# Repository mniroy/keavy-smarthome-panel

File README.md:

# KEAVY Smart Home Modular DIN-Rail & Standalone PLC Automation Platform

DRC-verified (0 violations, 0 unconnected items) industrial-grade DIN-Rail ESPHome & Home Assistant hardware ecosystem:

## 1. [`standalone/`](standalone/) — All-in-One 16-Channel LAN Relay Driver
- **Single-board `152.0 × 72.0 mm` (UM72 DIN-Rail)** exact replica of the 6-CH dimmer form factor.
- Built-in ESP32 DevKit + W5500 Ethernet LAN + `MCP23017` + `2× ULN2803G` + 16 status LEDs + 3.81mm screw terminals for **Omron G2R-1-E 24VDC NPN** relay modules.
- See [`standalone/README.md`](standalone/README.md).

## 2. [`modular/`](modular/) — Side-by-Side Chainable PLC Ecosystem (`KEAVY-BUS`, `DC3-10P`)
- Sized specifically to fit off-the-shelf DIN-Rail PLC enclosures (**SZOMK AK-P-08 `145×90×40mm`** & **AK-P-01 `115×90×40mm`**) as well as **UM72** carriers.
- Interconnected side-by-side via keyed, anti-reverse **Shrouded IDC Box Headers (`DC3-10P`, 2×5 2.54mm)** + standard `FC-10P` flat ribbon jumpers:
  - [`modular/brain/`](modular/brain/) — **KEAVY-BRAIN** (`120 × 72 mm`): ESP32 + W5500 LAN + 24V→5V Buck + `KEAVY-BUS` Master + Hot-Swap LDO & PTC
  - [`modular/relay_16ch/`](modular/relay_16ch/) — **KEAVY-RELAY16** (`96 × 72 mm`): 2500V Galvanic Isolated 16-CH NPN Relay Driver (`MCP23017` + `2× ULN2803G`, DIP `0x20–0x27`)
  - [`modular/dimmer_6ch/`](modular/dimmer_6ch/) — **KEAVY-DIMMER6** (`96 × 72 mm`): 2500V Galvanic Isolated 6-CH 60W/CH LED Dimmer (`PCA9685PW` + `6× AOD4184A`, DIP `0x40–0x47`)
  - [`modular/input_12a4/`](modular/input_12a4/) — **KEAVY-INPUT12A4** (`120 × 72 mm`): 12-CH Isolated Digital Inputs (Opto-Isolated 24V Dry/Wet) + 4-CH Industrial Analog Inputs (`ADS1115` 16-bit ADC, 0–10V / 4–20mA selectable)
- See [`modular/README.md`](modular/README.md).

## 3. [`PCB Design Rule/`](PCB%20Design%20Rule/) — Comprehensive PCB & EMI/EMC Design Guidelines
- Complete reference library covering:
  - `01-EMI-EMC-Certification-Rules.md`: Return paths, split-plane rules, certification checklists.
  - `02-Grounding-Return-Current-Stackup.md`: Star grounding, stitching vias, 2-layer and 4-layer stackups.
  - `03-Power-Integrity-Buck-Decoupling-Thermal.md`: SW node loop minimization, thermal vias, decoupling.
  - `04-High-Speed-Crystal-RF-Ethernet.md`: MII/RMII/SPI, differential impedance, isolation moat.
  - `05-Galvanic-Isolation-Creepage-Clearance-ESD.md`: IEC 60664-1 clearance/creepage, TVS diode layout.
  - `06-Routing-Geometry-DFM-DFA-JLCPCB.md`: Trace chamfering, acid traps, teardrops, SMD clearances.
  - `07-KEAVY-Project-Case-Study-and-Checklist.md`: Implementation record and DRC verification summary.
- See [`PCB Design Rule/README.md`](PCB%20Design%20Rule/README.md).

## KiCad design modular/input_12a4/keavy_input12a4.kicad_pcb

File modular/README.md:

# KEAVY Modular DIN-Rail PLC Ecosystem (REV 2.0 — Industrial Galvanic Isolation & Hot-Swap Bus)

A modular, side-by-side chainable **DIN-Rail Smart Automation Ecosystem** built for **ESPHome** and **Home Assistant**, sized to fit off-the-shelf **PLC DIN-Rail Enclosures** (`SZOMK AK-P-08` & `AK-P-01`) as well as open **UM72 (72mm)** DIN-Rail carriers.

---

## REV 2.0 Industrial Upgrades

1. **Full 2500 Vrms Galvanic Isolation (`ADuM1250ARZ` + `B0505S-1W`) on Every Slave Module**:
   - **Zero Ground Loop**: Bus ground (`GND_BUS`) and 24V high-current power ground (`GND_ISO`) are **100% electrically separated** on both `KEAVY-RELAY16` and `KEAVY-DIMMER6`.
   - **Isolated Power**: Each slave uses a `B0505S-1W` (5V→5V 1W isolated DC-DC) + local `AMS1117-3.3` (`+3V3_ISO`) to power its `MCP23017` / `PCA9685PW` and `ADuM1250ARZ` Side 2.
   - **Isolated Bidirectional I²C**: `ADuM1250ARZ` (pin-compatible with `ISO1540DR` / `CA-IS3020S`) isolates `SDA` & `SCL` up to 2500 Vrms with dedicated `4.7kΩ` pull-ups on the isolated side.
2. **Hot-Swap & Short-Circuit Protection on `KEAVY-BRAIN`**:
   - **Dedicated Bus LDO (`U5_BUS`, `AMS1117-3.3`)**: `+3V3_BUS` is generated independently from the ESP32 DevKit's internal 3.3V regulator — hot-plugging or shorting a slave module will **not** brownout or reset the ESP32.
   - **Dual 500mA SMD PTC Polyfuses (`F_5V`, `F_3V3`)**: Auto-resetting overcurrent protection on both `+5V_BUS` and `+3V3_BUS`.
3. **EMI & ESD Hardening for Relay/Contactor Panels**:
   - **EMI-Shielded `DC3-10P` Pinout**: `GND_BUS` (Pin 8) physically separates `I2C_SDA` (Pin 7) from `I2C_SCL` (Pin 9) inside the 10-pin IDC ribbon cable.
   - **Strong `2.2kΩ` Pull-Ups + `47Ω` Series Damping Resistors** (`R_DSDA`, `R_DSCL`) + **`USBLC6-2SC6` ESD TVS Diode** (`D_ESD`) right at the `J_BUS_OUT` connector.
   - **100 kHz I²C Bus Clock** configured in [`firmware/keavy_modular.yaml`](firmware/keavy_modular.yaml) for maximum noise margin.

---

## System Architecture (`KEAVY-BUS` REV 2.0)

```
┌───────────────────────────┐   DC3-10P IDC    ┌────────────────────────┐   DC3-10P IDC    ┌────────────────────────┐
│     KEAVY-BRAIN V2.0      │ ═══════════════▶ │   KEAVY-RELAY16 V2.0   │ ═══════════════▶ │   KEAVY-DIMMER6 V2.0   │
│  120.0 × 72.0 mm          │  (Hot-Swap Bus)  │   96.0 × 72.0 mm       │  (Hot-Swap Bus)  │   96.0 × 72.0 mm       │
│  ESP32 + W5500 + U5_BUS   │                  │  2500V ISO (ADuM1250 + │                  │  2500V ISO (ADuM1250 + │
│  2×500mA PTC + USBLC6 ESD │                  │  B0505S) + MCP23017 +  │                  │  B0505S) + PCA9685 +   │
│  Fits: AK-P-08 / UM72     │                  │  2×ULN2803G (16-CH)    │                  │  6×AOD4184A (60W/CH)   │
└───────────────────────────┘                  └────────────────────────┘                  └────────────────────────┘
```

### Modules Included (All 0 DRC Violations, 0 Unconnected Items)

| Module | PCB Size | Market PLC Casing Fit | Function | Addressing / Scalability |
|---|---|---|---|---|
| **KEAVY-BRAIN** | `120.0 × 72.0 mm` | **SZOMK AK-P-08** (`145×90×40mm`) & **UM72** | ESP32 DevKit + W5500 LAN + RJ45 + 24V→5V Buck (`XL1509-5.0`) + Dedicated `U5_BUS` 3.3V + Dual `500mA PTC` + `USBLC6-2SC6` ESD | 1 Brain per bus (1 Ethernet cable) |
| **KEAVY-RELAY16** | `96.0 × 72.0 mm` | **SZOMK AK-P-01** (`115×90×40mm`) & **UM72** | **2500Vrms Isolated** 16-CH 24VDC NPN Relay Driver (`B0505S-1W` + `ADuM1250ARZ` + `MCP23017` + `2× ULN2803G`) for Omron G2R-1-E | 3-bit DIP `SW1`: `0x20`–`0x27` (up to **8 boards = 128 relays**) |
| **KEAVY-DIMMER6** | `96.0 × 72.0 mm` | **SZOMK AK-P-01** (`115×90×40mm`) & **UM72** | **2500Vrms Isolated** 6-CH 60W/CH LED Dimmer (`B0505S-1W` + `ADuM1250ARZ` + `PCA9685PW` 1.526kHz + `6× AOD4184A`, 15A fuse) | 3-bit DIP `SW1`: `0x40`–`0x47` (up to **8 boards = 48 dimmers**) |
| **KEAVY-INPUT12A4** | `120.0 × 72.0 mm` | **SZOMK AK-P-08** (`145×90×40mm`) & **UM72** | **2500Vrms Isolated** 12-CH DI (3× `TLP281-4` optocouplers) + 4-CH Industrial AI (`ADS1115` 16-bit ADC, 0–10V / 4–20mA selectable) + `ADuM1250ARZ` + `B0505S-1W` | `MCP23017` DIP `0x20`–`0x27`, `ADS1115` ADDR Pin `0x48`–`0x4B` |

### Standardized 10-Pin `KEAVY-BUS` REV 2.0 (`DC3-10P` Shrouded Keyed IDC Header)

| Pin | Signal | Pin | Signal |
|---|---|---|---|
| **1** | `+5V_BUS` (500mA PTC) | **2** | `+5V_BUS` (500mA PTC) |
| **3** | `GND_BUS` | **4** | `GND_BUS` |
| **5** | `+3V3_BUS` (Dedicated LDO + 500mA PTC) | **6** | `GND_BUS` (Shield) |
| **7** | `I2C_SDA` (`GPIO21`, 47Ω + ESD) | **8** | `GND_BUS` **(EMI Shield between SDA & SCL)** |
| **9** | `I2C_SCL` (`GPIO22`, 47Ω + ESD) | **10** | `BUS_INT` (`GPIO16`) |

*(High-current 24V coil/LED power is fed separately to each slave module's own `J1` 24V terminal block, with `GND_ISO` 100% galvanically isolated from `GND_BUS`.)*

---

## Firmware & Manufacturing Files

- **Unified ESPHome Config (100 kHz I²C)**: [`firmware/keavy_modular.yaml`](firmware/keavy_modular.yaml)
- **JLCPCB Packages** (Gerber ZIP + BOM with LCSC Part # + CPL):
  - `brain/manufacturing/jlcpcb/`
  - `relay_16ch/manufacturing/jlcpcb/`
  - `dimmer_6ch/manufacturing/jlcpcb/`

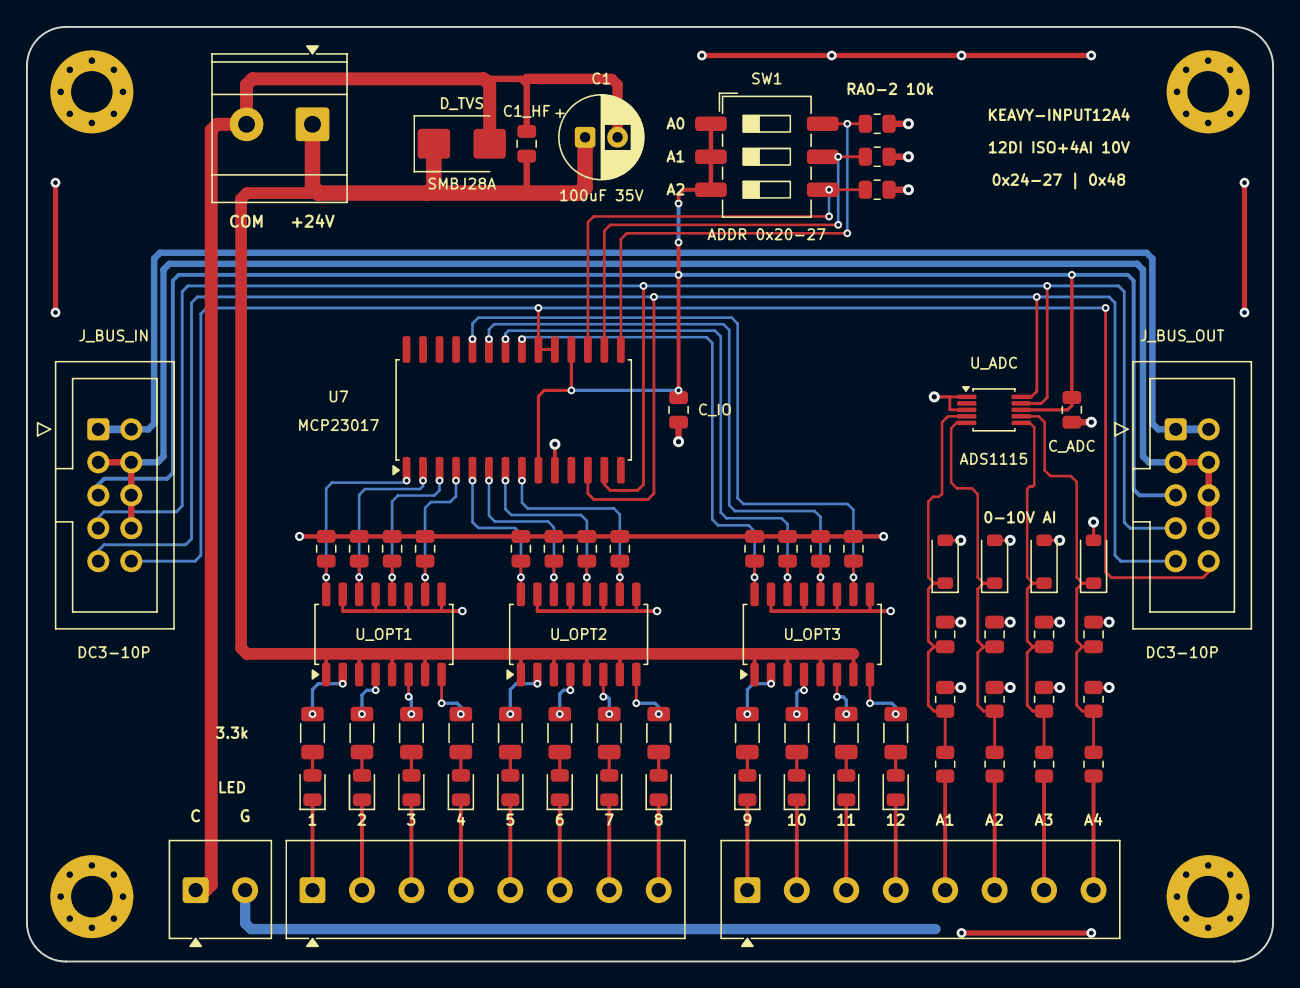
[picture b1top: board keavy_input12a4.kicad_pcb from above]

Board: 2 copper layers, 96.0 x 72.0 mm, 76 parts (0 on the bottom side), 67 nets.

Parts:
C1: 100uF 35V; CP_Radial_D6.3mm_P2.50mm
C1_HF: 100nF 50V; C_0805_2012Metric
CA1, CA2, CA3, CA4: 100nF; C_0805_2012Metric
CD1, CD2, CD3, CD4, CD5, CD6, CD7, CD8, CD9, CD10, CD11, CD12: 100nF; C_0805_2012Metric
C_ADC: 100nF; C_0805_2012Metric
C_IO: 100nF; C_0805_2012Metric
DA1, DA2, DA3, DA4: BZT52C3V3; D_SOD-123
D_TVS: SMBJ28A; D_SMB
H1, H2, H3, H4: M3; MountingHole_3.2mm_M3_Pad_Via
J1: 24V_IN; TerminalBlock_Phoenix_MKDS-3-2-5.08_1x02_P5.08mm_Horizontal
J2: COM_GND; TerminalBlock_Phoenix_MKDS-1-2-3.81_1x02_P3.81mm_Horizontal
J3: DI1-DI8; TerminalBlock_Phoenix_MKDS-1-8-3.81_1x08_P3.81mm_Horizontal
J4: DI9-12_AI1-4; TerminalBlock_Phoenix_MKDS-1-8-3.81_1x08_P3.81mm_Horizontal
J_BUS_IN: DC3-10P; IDC-Header_2x05_P2.54mm_Vertical
J_BUS_OUT: DC3-10P; IDC-Header_2x05_P2.54mm_Vertical
LED1, LED2, LED3, LED4, LED5, LED6, LED7, LED8, LED9, LED10, LED11, LED12: LED; LED_0805_2012Metric
RA0, RA1, RA2: 10k; R_0805_2012Metric
RAH1, RAH2, RAH3, RAH4: 22k 1%; R_0805_2012Metric
RAL1, RAL2, RAL3, RAL4: 10k 1%; R_0805_2012Metric
RD1, RD2, RD3, RD4, RD5, RD6, RD7, RD8, RD9, RD10, RD11, RD12: 3.3k; R_1206_3216Metric
SW1: ADDR 0x20-27; SW_DIP_SPSTx03_Slide_6.7x9.18mm_W8.61mm_P2.54mm_LowProfile
U7: MCP23017; SOIC-28W_7.5x17.9mm_P1.27mm
U_ADC: ADS1115; MSOP-10_3x3mm_P0.5mm
U_OPT1, U_OPT2, U_OPT3: TLP281-4; SOP-16_4.4x10.4mm_P1.27mm

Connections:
+3V3_BUS: C_ADC.1, C_IO.1, J_BUS_IN.5, J_BUS_OUT.5, SW1.1, SW1.2, SW1.3, U7.9, U7.18, U_ADC.8
+5V_BUS: J_BUS_IN.1, J_BUS_IN.2, J_BUS_OUT.1, J_BUS_OUT.2
+24V_FIELD: C1.1, C1_HF.1, D_TVS.1, J1.1, U_OPT1.1, U_OPT1.3, U_OPT1.5, U_OPT1.7, U_OPT2.1, U_OPT2.3, U_OPT2.5, U_OPT2.7, U_OPT3.1, U_OPT3.3, U_OPT3.5, U_OPT3.7
ADC_AIN0: CA1.1, DA1.1, RAH1.2, RAL1.1, U_ADC.4
ADC_AIN1: CA2.1, DA2.1, RAH2.2, RAL2.1, U_ADC.5
ADC_AIN2: CA3.1, DA3.1, RAH3.2, RAL3.1, U_ADC.6
ADC_AIN3: CA4.1, DA4.1, RAH4.2, RAL4.1, U_ADC.7
ADDR_A0: RA0.1, SW1.6, U7.15
ADDR_A1: RA1.1, SW1.5, U7.16
ADDR_A2: RA2.1, SW1.4, U7.17
AI1_0_10V: J4.5, RAH1.1
AI2_0_10V: J4.6, RAH2.1
AI3_0_10V: J4.7, RAH3.1
AI4_0_10V: J4.8, RAH4.1
BUS_INT: J_BUS_IN.10, J_BUS_OUT.10, U7.19, U7.20
DI1_FIELD: J3.1, LED1.1
DI1_LED: LED1.2, RD1.2
DI1_MCU: CD1.1, U7.1, U_OPT1.16
DI1_OPTO_A: RD1.1, U_OPT1.2
DI2_FIELD: J3.2, LED2.1
DI2_LED: LED2.2, RD2.2
DI2_MCU: CD2.1, U7.2, U_OPT1.14
DI2_OPTO_A: RD2.1, U_OPT1.4
DI3_FIELD: J3.3, LED3.1
DI3_LED: LED3.2, RD3.2
DI3_MCU: CD3.1, U7.3, U_OPT1.12
DI3_OPTO_A: RD3.1, U_OPT1.6
DI4_FIELD: J3.4, LED4.1
DI4_LED: LED4.2, RD4.2
DI4_MCU: CD4.1, U7.4, U_OPT1.10
DI4_OPTO_A: RD4.1, U_OPT1.8
DI5_FIELD: J3.5, LED5.1
DI5_LED: LED5.2, RD5.2
DI5_MCU: CD5.1, U7.5, U_OPT2.16
DI5_OPTO_A: RD5.1, U_OPT2.2
DI6_FIELD: J3.6, LED6.1
DI6_LED: LED6.2, RD6.2
DI6_MCU: CD6.1, U7.6, U_OPT2.14
DI6_OPTO_A: RD6.1, U_OPT2.4
DI7_FIELD: J3.7, LED7.1
DI7_LED: LED7.2, RD7.2
DI7_MCU: CD7.1, U7.7, U_OPT2.12
DI7_OPTO_A: RD7.1, U_OPT2.6
DI8_FIELD: J3.8, LED8.1
DI8_LED: LED8.2, RD8.2
DI8_MCU: CD8.1, U7.8, U_OPT2.10
DI8_OPTO_A: RD8.1, U_OPT2.8
DI9_FIELD: J4.1, LED9.1
DI9_LED: LED9.2, RD9.2
DI9_MCU: CD9.1, U7.21, U_OPT3.16
DI9_OPTO_A: RD9.1, U_OPT3.2
DI10_FIELD: J4.2, LED10.1
DI10_LED: LED10.2, RD10.2
DI10_MCU: CD10.1, U7.22, U_OPT3.14
DI10_OPTO_A: RD10.1, U_OPT3.4
DI11_FIELD: J4.3, LED11.1
DI11_LED: LED11.2, RD11.2
DI11_MCU: CD11.1, U7.23, U_OPT3.12
DI11_OPTO_A: RD11.1, U_OPT3.6
DI12_FIELD: J4.4, LED12.1
DI12_LED: LED12.2, RD12.2
DI12_MCU: CD12.1, U7.24, U_OPT3.10
DI12_OPTO_A: RD12.1, U_OPT3.8
GND_BUS: CA1.2, CA2.2, CA3.2, CA4.2, CD1.2, CD2.2, CD3.2, CD4.2, CD5.2, CD6.2, CD7.2, CD8.2, CD9.2, CD10.2, CD11.2, CD12.2, C_ADC.2, C_IO.2, DA1.2, DA2.2, DA3.2, DA4.2, H1.1, H2.1, H3.1, H4.1, J2.2, J_BUS_IN.3, J_BUS_IN.4, J_BUS_IN.6, J_BUS_IN.8, J_BUS_OUT.3, J_BUS_OUT.4, J_BUS_OUT.6, J_BUS_OUT.8, RA0.2, RA1.2, RA2.2, RAL1.2, RAL2.2, RAL3.2, RAL4.2, U7.10, U_ADC.1, U_ADC.3, U_OPT1.9, U_OPT1.11, U_OPT1.13, U_OPT1.15, U_OPT2.9, U_OPT2.11, U_OPT2.13, U_OPT2.15, U_OPT3.9, U_OPT3.11, U_OPT3.13, U_OPT3.15
GND_FIELD: C1.2, C1_HF.2, D_TVS.2, J1.2, J2.1
I2C_SCL: J_BUS_IN.9, J_BUS_OUT.9, U7.12, U_ADC.10
I2C_SDA: J_BUS_IN.7, J_BUS_OUT.7, U7.13, U_ADC.9

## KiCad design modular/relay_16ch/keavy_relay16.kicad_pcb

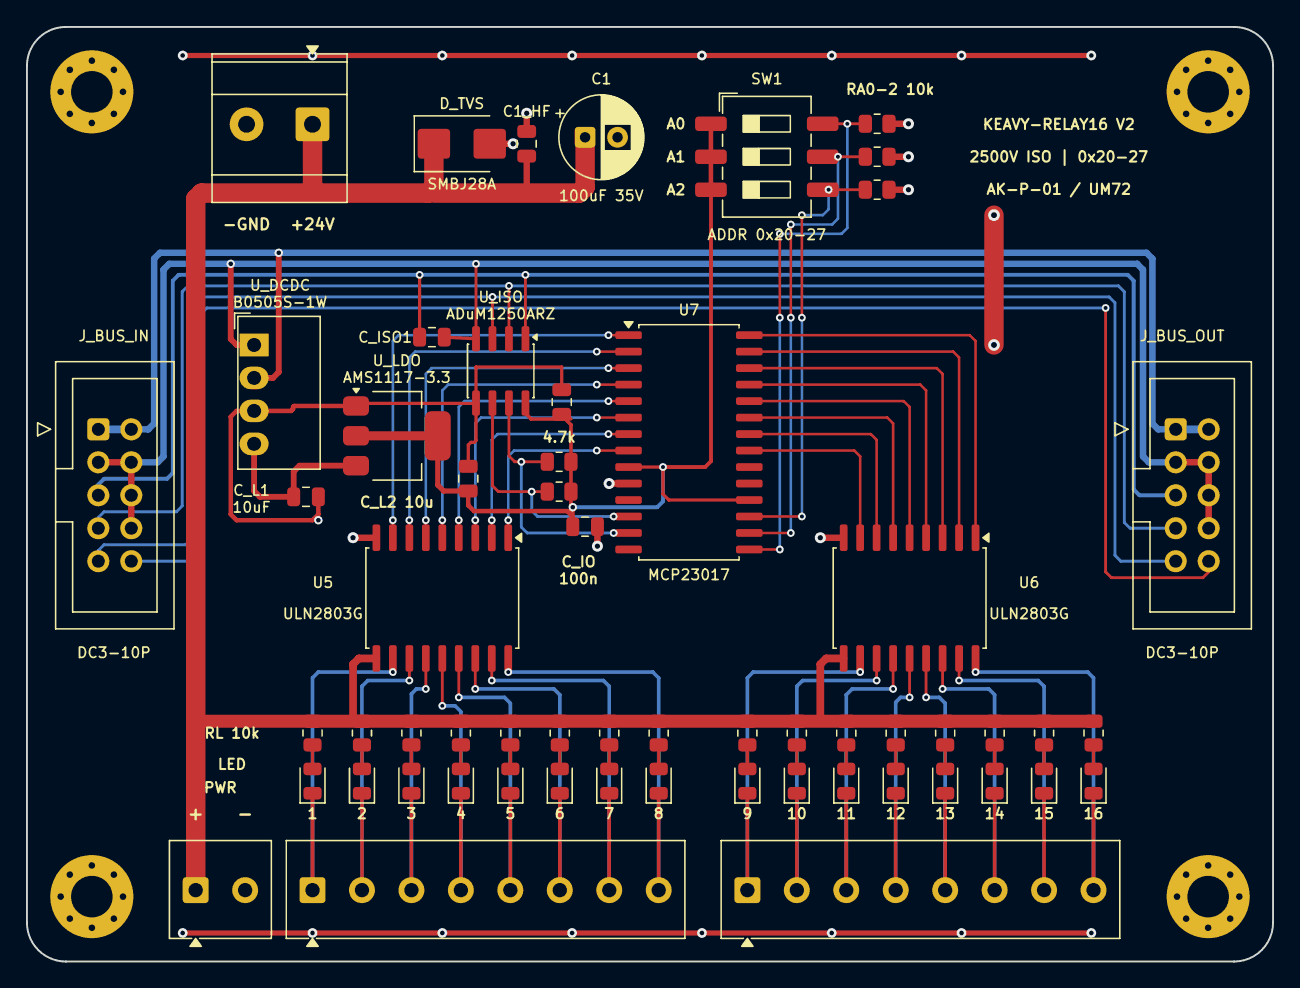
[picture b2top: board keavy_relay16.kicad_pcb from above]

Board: 2 copper layers, 96.0 x 72.0 mm, 62 parts (0 on the bottom side), 63 nets.

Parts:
C1: 100uF 35V; CP_Radial_D6.3mm_P2.50mm
C1_HF: 100nF 50V; C_0805_2012Metric
C_IO: 100nF; C_0805_2012Metric
C_ISO1, C_ISO2: 100nF; C_0805_2012Metric
C_L1, C_L2: 10uF; C_0805_2012Metric
D_TVS: SMBJ28A; D_SMB
H1, H2, H3, H4: M3; MountingHole_3.2mm_M3_Pad_Via
J1: 24V_IN; TerminalBlock_Phoenix_MKDS-3-2-5.08_1x02_P5.08mm_Horizontal
J2: 24V_OUT; TerminalBlock_Phoenix_MKDS-1-2-3.81_1x02_P3.81mm_Horizontal
J3: CH1-CH8; TerminalBlock_Phoenix_MKDS-1-8-3.81_1x08_P3.81mm_Horizontal
J4: CH9-CH16; TerminalBlock_Phoenix_MKDS-1-8-3.81_1x08_P3.81mm_Horizontal
J_BUS_IN: DC3-10P; IDC-Header_2x05_P2.54mm_Vertical
J_BUS_OUT: DC3-10P; IDC-Header_2x05_P2.54mm_Vertical
LED1, LED2, LED3, LED4, LED5, LED6, LED7, LED8, LED9, LED10, LED11, LED12, LED13, LED14, LED15, LED16: LED; LED_0805_2012Metric
RA0, RA1, RA2: 10k; R_0805_2012Metric
RL1, RL2, RL3, RL4, RL5, RL6, RL7, RL8, RL9, RL10, RL11, RL12, RL13, RL14, RL15, RL16: 10k; R_0805_2012Metric
R_ISCL: 4.7k; R_0805_2012Metric
R_ISDA: 4.7k; R_0805_2012Metric
SW1: ADDR 0x20-27; SW_DIP_SPSTx03_Slide_6.7x9.18mm_W8.61mm_P2.54mm_LowProfile
U5, U6: ULN2803G; SOIC-18W_7.5x11.6mm_P1.27mm
U7: MCP23017; SOIC-28W_7.5x17.9mm_P1.27mm
U_DCDC: B0505S-1W; Converter_DCDC_Murata_MEE1SxxxxSC_THT
U_ISO: ADuM1250ARZ; SOIC-8_3.9x4.9mm_P1.27mm
U_LDO: AMS1117-3.3; SOT-223-3_TabPin2

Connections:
+3V3_BUS: C_ISO1.2, J_BUS_IN.5, J_BUS_OUT.5, U_ISO.1
+3V3_ISO: C_IO.1, C_ISO2.1, C_L2.1, R_ISCL.1, R_ISDA.1, SW1.1, SW1.2, SW1.3, U7.9, U7.18, U_ISO.8, U_LDO.2
+5V_BUS: J_BUS_IN.1, J_BUS_IN.2, J_BUS_OUT.1, J_BUS_OUT.2, U_DCDC.2
+5V_ISO: C_L1.1, U_DCDC.4, U_LDO.3
+24V_BUS: C1.1, C1_HF.1, D_TVS.1, J1.1, J2.1, RL1.1, RL2.1, RL3.1, RL4.1, RL5.1, RL6.1, RL7.1, RL8.1, RL9.1, RL10.1, RL11.1, RL12.1, RL13.1, RL14.1, RL15.1, RL16.1, U5.10, U6.10
ADDR_A0: RA0.1, SW1.6, U7.15
ADDR_A1: RA1.1, SW1.5, U7.16
ADDR_A2: RA2.1, SW1.4, U7.17
BUS_INT: J_BUS_IN.10, J_BUS_OUT.10
CH1_NPN_OUT: J3.1, LED1.1, U5.11
CH2_NPN_OUT: J3.2, LED2.1, U5.12
CH3_NPN_OUT: J3.3, LED3.1, U5.13
CH4_NPN_OUT: J3.4, LED4.1, U5.14
CH5_NPN_OUT: J3.5, LED5.1, U5.15
CH6_NPN_OUT: J3.6, LED6.1, U5.16
CH7_NPN_OUT: J3.7, LED7.1, U5.17
CH8_NPN_OUT: J3.8, LED8.1, U5.18
CH9_NPN_OUT: J4.1, LED9.1, U6.11
CH10_NPN_OUT: J4.2, LED10.1, U6.12
CH11_NPN_OUT: J4.3, LED11.1, U6.13
CH12_NPN_OUT: J4.4, LED12.1, U6.14
CH13_NPN_OUT: J4.5, LED13.1, U6.15
CH14_NPN_OUT: J4.6, LED14.1, U6.16
CH15_NPN_OUT: J4.7, LED15.1, U6.17
CH16_NPN_OUT: J4.8, LED16.1, U6.18
GND_BUS: C_ISO1.1, J_BUS_IN.3, J_BUS_IN.4, J_BUS_IN.6, J_BUS_IN.8, J_BUS_OUT.3, J_BUS_OUT.4, J_BUS_OUT.6, J_BUS_OUT.8, U_DCDC.1, U_ISO.4
GND_ISO: C1.2, C1_HF.2, C_IO.2, C_ISO2.2, C_L1.2, C_L2.2, D_TVS.2, H1.1, H2.1, H3.1, H4.1, J1.2, J2.2, RA0.2, RA1.2, RA2.2, U5.9, U6.9, U7.10, U_DCDC.3, U_ISO.5, U_LDO.1
I2C_SCL: J_BUS_IN.9, J_BUS_OUT.9, U_ISO.3
I2C_SDA: J_BUS_IN.7, J_BUS_OUT.7, U_ISO.2
ISO_SCL: R_ISCL.2, U7.12, U_ISO.6
ISO_SDA: R_ISDA.2, U7.13, U_ISO.7
LED_CH1_A: LED1.2, RL1.2
LED_CH2_A: LED2.2, RL2.2
LED_CH3_A: LED3.2, RL3.2
LED_CH4_A: LED4.2, RL4.2
LED_CH5_A: LED5.2, RL5.2
LED_CH6_A: LED6.2, RL6.2
LED_CH7_A: LED7.2, RL7.2
LED_CH8_A: LED8.2, RL8.2
LED_CH9_A: LED9.2, RL9.2
LED_CH10_A: LED10.2, RL10.2
LED_CH11_A: LED11.2, RL11.2
LED_CH12_A: LED12.2, RL12.2
LED_CH13_A: LED13.2, RL13.2
LED_CH14_A: LED14.2, RL14.2
LED_CH15_A: LED15.2, RL15.2
LED_CH16_A: LED16.2, RL16.2
RELAY_CH1: U5.8, U7.1
RELAY_CH2: U5.7, U7.2
RELAY_CH3: U5.6, U7.3
RELAY_CH4: U5.5, U7.4
RELAY_CH5: U5.4, U7.5
RELAY_CH6: U5.3, U7.6
RELAY_CH7: U5.2, U7.7
RELAY_CH8: U5.1, U7.8
RELAY_CH9: U6.8, U7.21
RELAY_CH10: U6.7, U7.22
RELAY_CH11: U6.6, U7.23
RELAY_CH12: U6.5, U7.24
RELAY_CH13: U6.4, U7.25
RELAY_CH14: U6.3, U7.26
RELAY_CH15: U6.2, U7.27
RELAY_CH16: U6.1, U7.28

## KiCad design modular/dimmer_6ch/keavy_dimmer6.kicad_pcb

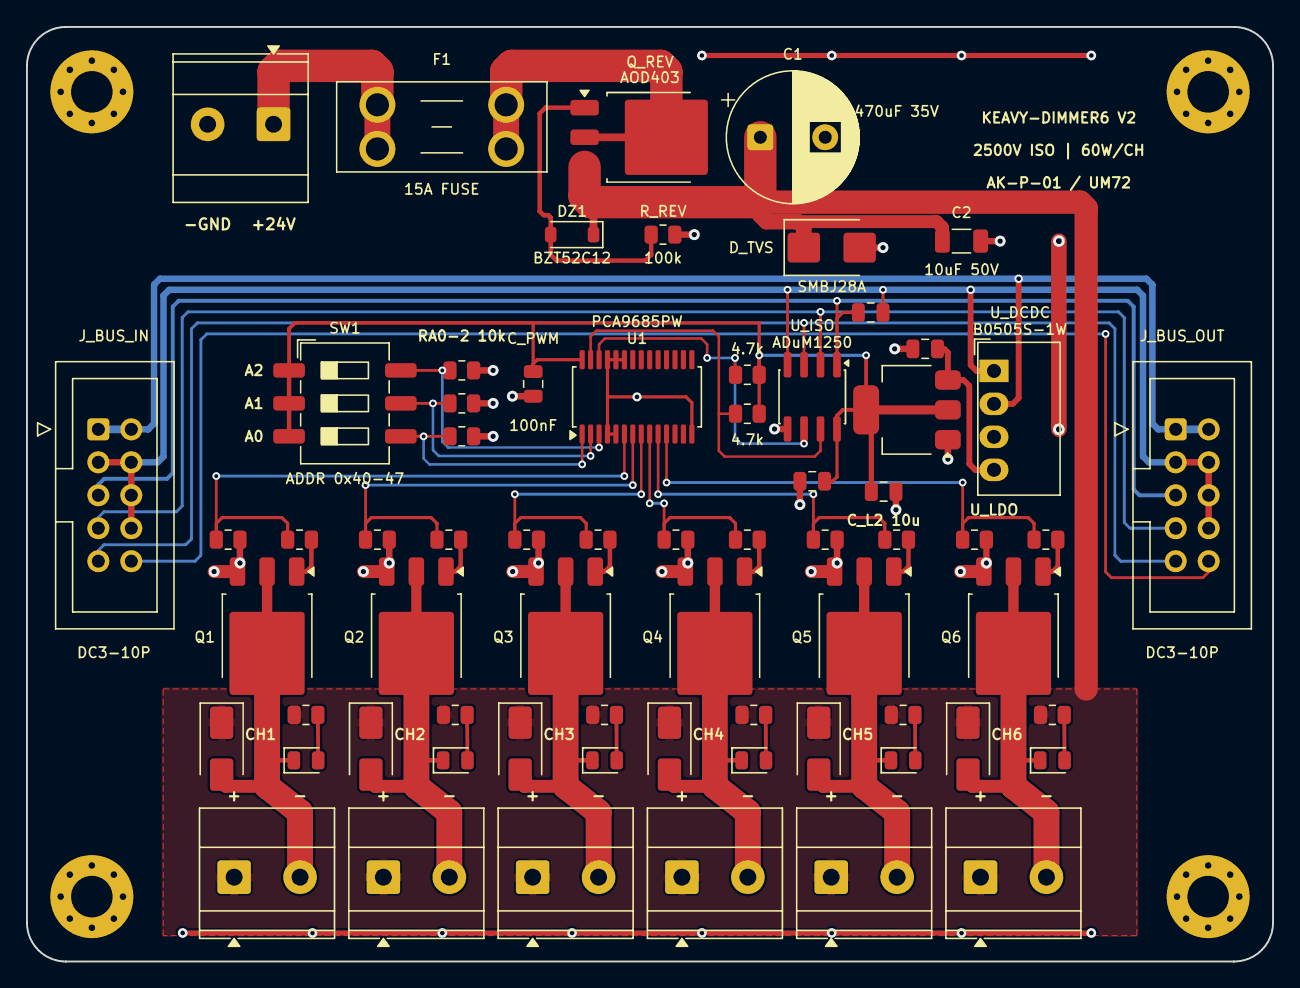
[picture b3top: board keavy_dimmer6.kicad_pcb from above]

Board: 2 copper layers, 96.0 x 72.0 mm, 71 parts (0 on the bottom side), 42 nets.

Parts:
C1: 470uF 35V; CP_Radial_D10.0mm_P5.00mm
C2: 10uF 50V; C_1206_3216Metric
C_ISO1, C_ISO2: 100nF; C_0805_2012Metric
C_L1, C_L2: 10uF; C_0805_2012Metric
C_PWM: 100nF; C_0805_2012Metric
D1, D2, D3, D4, D5, D6: SS34; D_SMA
DZ1: BZT52C12; D_SOD-123
D_TVS: SMBJ28A; D_SMB
F1: 15A FUSE; Fuseholder_Blade_Mini_Keystone_3568
H1, H2, H3, H4: M3; MountingHole_3.2mm_M3_Pad_Via
J1: 24V_IN; TerminalBlock_Phoenix_MKDS-3-2-5.08_1x02_P5.08mm_Horizontal
J2: CH1; TerminalBlock_Phoenix_MKDS-1,5-2-5.08_1x02_P5.08mm_Horizont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
J3: CH2; TerminalBlock_Phoenix_MKDS-1,5-2-5.08_1x02_P5.08mm_Horizont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
J4: CH3; TerminalBlock_Phoenix_MKDS-1,5-2-5.08_1x02_P5.08mm_Horizont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
J5: CH4; TerminalBlock_Phoenix_MKDS-1,5-2-5.08_1x02_P5.08mm_Horizont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
J6: CH5; TerminalBlock_Phoenix_MKDS-1,5-2-5.08_1x02_P5.08mm_Horizont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
J7: CH6; TerminalBlock_Phoenix_MKDS-1,5-2-5.08_1x02_P5.08mm_Horizont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
J_BUS_IN: DC3-10P; IDC-Header_2x05_P2.54mm_Vertical
J_BUS_OUT: DC3-10P; IDC-Header_2x05_P2.54mm_Vertical
LED1, LED2, LED3, LED4, LED5, LED6: LED; LED_0805_2012Metric
Q1, Q2, Q3, Q4, Q5, Q6: AOD4184A; TO-252-3_TabPin2
Q_REV: AOD403; TO-252-3_TabPin2
R1, R3, R5, R7, R9, R11: 100R; R_0805_2012Metric
R2, R4, R6, R8, R10, R12: 10k; R_0805_2012Metric
RA0, RA1, RA2: 10k; R_0805_2012Metric
RL1, RL2, RL3, RL4, RL5, RL6: 10k; R_0805_2012Metric
R_ISCL: 4.7k; R_0805_2012Metric
R_ISDA: 4.7k; R_0805_2012Metric
R_REV: 100k; R_0805_2012Metric
SW1: ADDR 0x40-47; SW_DIP_SPSTx03_Slide_6.7x9.18mm_W8.61mm_P2.54mm_LowProfile
U1: PCA9685PW; TSSOP-28_4.4x9.7mm_P0.65mm
U_DCDC: B0505S-1W; Converter_DCDC_Murata_MEE1SxxxxSC_THT
U_ISO: ADuM1250; SOIC-8_3.9x4.9mm_P1.27mm
U_LDO: AMS1117-3.3; SOT-223-3_TabPin2

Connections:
+3V3_BUS: C_ISO1.1, J_BUS_IN.5, J_BUS_OUT.5, U_ISO.1
+3V3_ISO: C_ISO2.2, C_L2.1, C_PWM.1, R_ISCL.1, R_ISDA.1, SW1.1, SW1.2, SW1.3, U1.28, U_ISO.8, U_LDO.2
+5V_BUS: J_BUS_IN.1, J_BUS_IN.2, J_BUS_OUT.1, J_BUS_OUT.2, U_DCDC.2
+5V_ISO: C_L1.1, U_DCDC.4, U_LDO.3
+24V_BUS: C1.1, C2.1, D1.1, D2.1, D3.1, D4.1, D5.1, D6.1, DZ1.1, D_TVS.1, J2.1, J3.1, J4.1, J5.1, J6.1, J7.1, Q_REV.3, RL1.1, RL2.1, RL3.1, RL4.1, RL5.1, RL6.1
+24V_FUSED: F1.2, Q_REV.2
+24V_IN: F1.1, J1.1
ADDR_A0: RA0.1, SW1.4, U1.1
ADDR_A1: RA1.1, SW1.5, U1.2
ADDR_A2: RA2.1, SW1.6, U1.3
BUS_INT: J_BUS_IN.10, J_BUS_OUT.10
CH1_OUT-: D1.2, J2.2, LED1.1, Q1.2
CH2_OUT-: D2.2, J3.2, LED2.1, Q2.2
CH3_OUT-: D3.2, J4.2, LED3.1, Q3.2
CH4_OUT-: D4.2, J5.2, LED4.1, Q4.2
CH5_OUT-: D5.2, J6.2, LED5.1, Q5.2
CH6_OUT-: D6.2, J7.2, LED6.1, Q6.2
GATE_CH1: Q1.1, R1.2
GATE_CH2: Q2.1, R3.2
GATE_CH3: Q3.1, R5.2
GATE_CH4: Q4.1, R7.2
GATE_CH5: Q5.1, R9.2
GATE_CH6: Q6.1, R11.2
GND_BUS: C_ISO1.2, J_BUS_IN.3, J_BUS_IN.4, J_BUS_IN.6, J_BUS_IN.8, J_BUS_OUT.3, J_BUS_OUT.4, J_BUS_OUT.6, J_BUS_OUT.8, U_DCDC.1, U_ISO.4
GND_ISO: C1.2, C2.2, C_ISO2.1, C_L1.2, C_L2.2, C_PWM.2, D_TVS.2, H1.1, H2.1, H3.1, H4.1, J1.2, Q1.3, Q2.3, Q3.3, Q4.3, Q5.3, Q6.3, R2.2, R4.2, R6.2, R8.2, R10.2, R12.2, RA0.2, RA1.2, RA2.2, R_REV.2, U1.4, U1.5, U1.14, U1.23, U1.24, U1.25, U_DCDC.3, U_ISO.5, U_LDO.1
I2C_SCL: J_BUS_IN.9, J_BUS_OUT.9, U_ISO.3
I2C_SDA: J_BUS_IN.7, J_BUS_OUT.7, U_ISO.2
ISO_SCL: R_ISCL.2, U1.26, U_ISO.6
ISO_SDA: R_ISDA.2, U1.27, U_ISO.7
LED_CH1_A: LED1.2, RL1.2
LED_CH2_A: LED2.2, RL2.2
LED_CH3_A: LED3.2, RL3.2
LED_CH4_A: LED4.2, RL4.2
LED_CH5_A: LED5.2, RL5.2
LED_CH6_A: LED6.2, RL6.2
PWM_CH1: R1.1, R2.1, U1.6
PWM_CH2: R3.1, R4.1, U1.7
PWM_CH3: R5.1, R6.1, U1.8
PWM_CH4: R7.1, R8.1, U1.9
PWM_CH5: R9.1, R10.1, U1.10
PWM_CH6: R11.1, R12.1, U1.11
REV_GATE: DZ1.2, Q_REV.1, R_REV.1

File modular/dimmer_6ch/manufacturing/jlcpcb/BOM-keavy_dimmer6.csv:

Comment,Designator,Footprint,LCSC Part #
470uF 35V,C1,CP_Radial_D10.0mm_P5.00mm,C331317
10uF 50V,C2,C_1206_3216Metric,C13585
100nF,"C_ISO1,C_ISO2,C_PWM",C_0805_2012Metric,C49678
10uF,"C_L1,C_L2",C_0805_2012Metric,C15850
SS34,"D1,D2,D3,D4,D5,D6",D_SMA,C2400
BZT52C12,DZ1,D_SOD-123,C80671
SMBJ28A,D_TVS,D_SMB,C98226
15A FUSE,F1,Fuseholder_Blade_Mini_Keystone_3568,C236378
24V_IN,J1,TerminalBlock_Phoenix_MKDS-3-2-5.08_1x02_P5.08mm_Horizontal,C8465
CH1,J2,"TerminalBlock_Phoenix_MKDS-1,5-2-5.08_1x02_P5.08mm_Horizontal",C8465
CH2,J3,"TerminalBlock_Phoenix_MKDS-1,5-2-5.08_1x02_P5.08mm_Horizontal",C8465
CH3,J4,"TerminalBlock_Phoenix_MKDS-1,5-2-5.08_1x02_P5.08mm_Horizontal",C8465
CH4,J5,"TerminalBlock_Phoenix_MKDS-1,5-2-5.08_1x02_P5.08mm_Horizontal",C8465
CH5,J6,"TerminalBlock_Phoenix_MKDS-1,5-2-5.08_1x02_P5.08mm_Horizontal",C8465
CH6,J7,"TerminalBlock_Phoenix_MKDS-1,5-2-5.08_1x02_P5.08mm_Horizontal",C8465
DC3-10P,"J_BUS_IN,J_BUS_OUT",IDC-Header_2x05_P2.54mm_Vertical,C49661
LED,"LED1,LED2,LED3,LED4,LED5,LED6",LED_0805_2012Metric,C2297
AOD4184A,"Q1,Q2,Q3,Q4,Q5,Q6",TO-252-3_TabPin2,C428236
AOD403,Q_REV,TO-252-3_TabPin2,C28969
100R,"R1,R11,R3,R5,R7,R9",R_0805_2012Metric,C17414
10k,"R10,R12,R2,R4,R6,R8,RA0,RA1,RA2,RL1,RL2,RL3,RL4,RL5,RL6",R_0805_2012Metric,C17415
4.7k,"R_ISCL,R_ISDA",R_0805_2012Metric,C17673
100k,R_REV,R_0805_2012Metric,C17407
ADDR 0x40-47,SW1,SW_DIP_SPSTx03_Slide_6.7x9.18mm_W8.61mm_P2.54mm_LowProfile,C410099
PCA9685PW,U1,TSSOP-28_4.4x9.7mm_P0.65mm,C444771
B0505S-1W,U_DCDC,Converter_DCDC_Murata_MEE1SxxxxSC_THT,C18619
ADuM1250,U_ISO,SOIC-8_3.9x4.9mm_P1.27mm,
AMS1117-3.3,U_LDO,SOT-223-3_TabPin2,C6186

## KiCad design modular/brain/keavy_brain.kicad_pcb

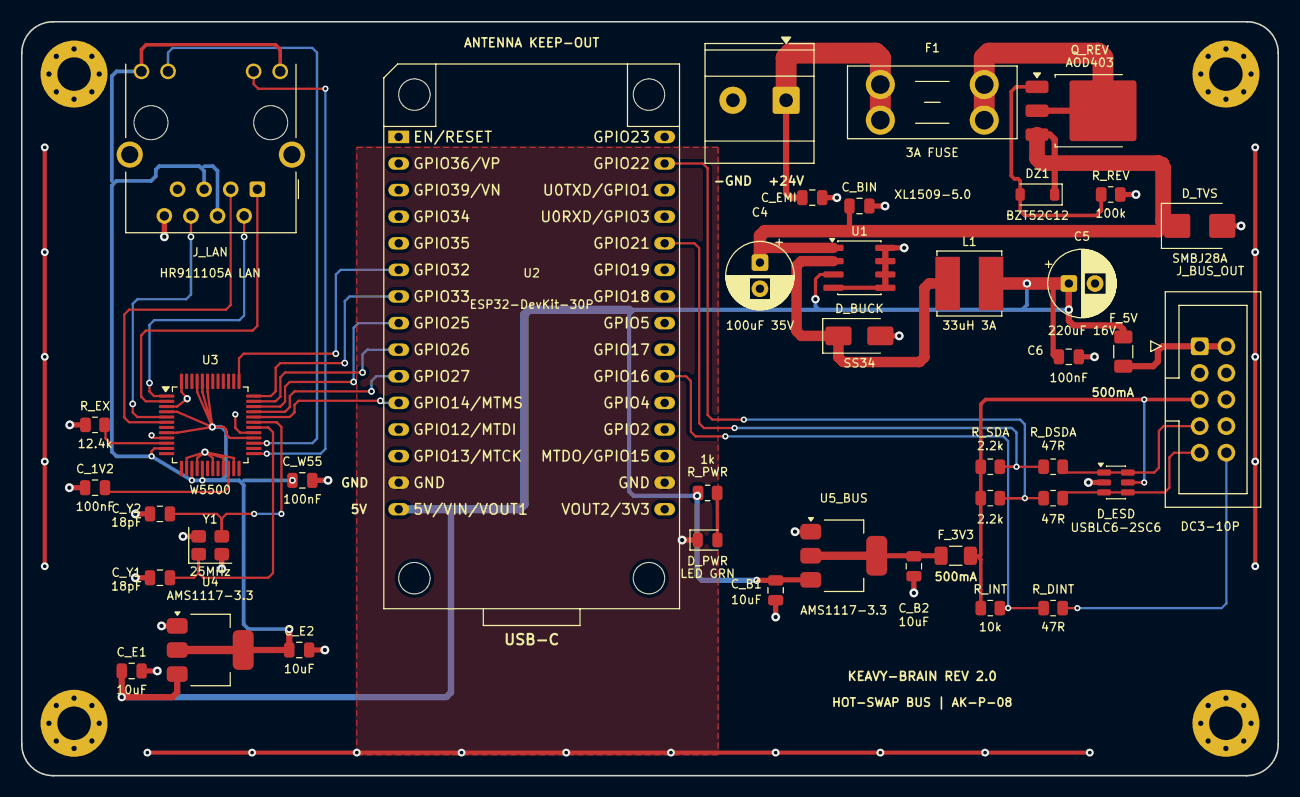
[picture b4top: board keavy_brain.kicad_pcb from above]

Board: 2 copper layers, 120.0 x 72.0 mm, 45 parts (0 on the bottom side), 34 nets.

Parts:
C4: 100uF 35V; CP_Radial_D6.3mm_P2.50mm
C5: 220uF 16V; CP_Radial_D6.3mm_P2.50mm
C6: 100nF; C_0805_2012Metric
C_1V2: 100nF; C_0805_2012Metric
C_B1, C_B2: 10uF; C_0805_2012Metric
C_BIN: 100nF 50V; C_0805_2012Metric
C_E1, C_E2: 10uF; C_0805_2012Metric
C_EMI: 100nF 50V; C_0805_2012Metric
C_W55: 100nF; C_0805_2012Metric
C_Y1, C_Y2: 18pF; C_0805_2012Metric
DZ1: BZT52C12; D_SOD-123
D_BUCK: SS34; D_SMA
D_ESD: USBLC6-2SC6; SOT-23-6
D_PWR: LED GRN; LED_0805_2012Metric
D_TVS: SMBJ28A; D_SMB
F1: 3A FUSE; Fuseholder_Blade_Mini_Keystone_3568
F_3V3, F_5V: 500mA PTC; Fuse_1206_3216Metric
H1, H2, H3, H4: M3; MountingHole_3.2mm_M3_Pad_Via
J1: 24V_IN; TerminalBlock_Phoenix_MKDS-3-2-5.08_1x02_P5.08mm_Horizontal
J_BUS_OUT: DC3-10P; IDC-Header_2x05_P2.54mm_Vertical
J_LAN: HR911105A LAN; RJ45_Hanrun_HR911105A_Horizontal
L1: 33uH 3A; L_Bourns_SRN6045TA
Q_REV: AOD403; TO-252-3_TabPin2
R_DINT: 47R; R_0805_2012Metric
R_DSCL: 47R; R_0805_2012Metric
R_DSDA: 47R; R_0805_2012Metric
R_EX: 12.4k; R_0805_2012Metric
R_INT: 10k; R_0805_2012Metric
R_PWR: 1k; R_0805_2012Metric
R_REV: 100k; R_0805_2012Metric
R_SCL: 2.2k; R_0805_2012Metric
R_SDA: 2.2k; R_0805_2012Metric
U1: XL1509-5.0; SOIC-8_3.9x4.9mm_P1.27mm
U2: ESP32-DevKit-30P; ESP32-DevKit-USB-C
U3: W5500; LQFP-48_7x7mm_P0.5mm
U4, U5_BUS: AMS1117-3.3; SOT-223-3_TabPin2
Y1: 25MHz; Crystal_SMD_3225-4Pin_3.2x2.5mm

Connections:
+3V3_BUS: D_ESD.5, F_3V3.2, J_BUS_OUT.5, R_INT.1, R_SCL.1, R_SDA.1
+3V3_B_RAW: C_B2.1, F_3V3.1, U5_BUS.2
+3V3_ETH: C_E2.1, C_W55.1, J_LAN.4, J_LAN.5, J_LAN.9, J_LAN.12, U3.4, U3.8, U3.11, U3.15, U3.17, U3.28, U3.43, U3.44, U3.45, U4.2
+5V: C5.1, C6.1, C_B1.1, C_E1.1, F_5V.1, L1.2, R_PWR.1, U1.3, U2.15, U4.3, U5_BUS.3
+5V_BUS: F_5V.2, J_BUS_OUT.1, J_BUS_OUT.2
+24V_BUS: C4.1, C_BIN.1, DZ1.1, D_TVS.1, Q_REV.3, U1.1
+24V_FUSED: F1.2, Q_REV.2
+24V_IN: C_EMI.1, F1.1, J1.1
BUCK_SW: D_BUCK.1, L1.1, U1.2
BUS_INT: J_BUS_OUT.10, R_DINT.2
ETH_1V2O: C_1V2.1, U3.22
ETH_ACT_LED: J_LAN.11, U3.27
ETH_CLK: U2.11, U3.32
ETH_CS: U2.10, U3.33
ETH_EXRES: R_EX.1, U3.10
ETH_INT: U2.7, U3.36
ETH_LINK_LED: J_LAN.10, U3.25
ETH_MISO: U2.8, U3.34
ETH_MOSI: U2.9, U3.35
ETH_RST: U2.6, U3.37
ETH_RXN: J_LAN.6, U3.5
ETH_RXP: J_LAN.3, U3.6
ETH_TXN: J_LAN.2, U3.1
ETH_TXP: J_LAN.1, U3.2
ETH_XI: C_Y1.1, U3.30, Y1.1
ETH_XO: C_Y2.1, U3.31, Y1.3
GND: C4.2, C5.2, C6.2, C_1V2.2, C_B1.2, C_B2.2, C_BIN.2, C_E1.2, C_E2.2, C_EMI.2, C_W55.2, C_Y1.2, C_Y2.2, D_BUCK.2, D_ESD.2, D_PWR.1, D_TVS.2, H1.1, H2.1, H3.1, H4.1, J1.2, J_BUS_OUT.3, J_BUS_OUT.4, J_BUS_OUT.6, J_BUS_OUT.8, J_LAN.8, J_LAN.SH, R_EX.2, R_REV.2, U1.4, U1.5, U1.6, U1.7, U1.8, U2.14, U2.17, U3.3, U3.9, U3.14, U3.16, U3.19, U3.21, U3.23, U3.29, U3.48, U4.1, U5_BUS.1, Y1.2, Y1.4
I2C_SCL: D_ESD.3, D_ESD.4, J_BUS_OUT.9, R_DSCL.2
I2C_SDA: D_ESD.1, D_ESD.6, J_BUS_OUT.7, R_DSDA.2
MCU_INT: R_DINT.1, R_INT.2, U2.21
MCU_SCL: R_DSCL.1, R_SCL.2, U2.29
MCU_SDA: R_DSDA.1, R_SDA.2, U2.26
PWR_LED_A: D_PWR.2, R_PWR.2
REV_GATE: DZ1.2, Q_REV.1, R_REV.1

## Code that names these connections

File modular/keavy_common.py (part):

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    """
    Assign standardized REV 2.0 10-pin KEAVY-BUS nets (DC3-10P, EMI-shielded):
      Pin 1,2 = +5V_BUS | Pin 3,4,6,8 = GND_BUS (Pin 8 shields SDA from SCL!)
      Pin 5   = +3V3_BUS | Pin 7 = I2C_SDA | Pin 9 = I2C_SCL | Pin 10 = BUS_INT
    """
    set_pad_net(fp, ["1", "2"], net_5v)
    set_pad_net(fp, ["3", "4", "6", "8"], net_gnd)
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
